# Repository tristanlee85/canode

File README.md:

# canode: dual-CAN vehicle interface

A small STM32G0B1 board with **two CAN channels**, USB-C and a 12 V automotive input, for sniffing, gatewaying and inline (man-in-the-middle) modification of vehicle CAN traffic. CAN1 faces the car, CAN2 faces the module. A typical job: suppress auto start-stop or change a body-module behaviour without touching the factory wiring.

Target vehicles: 2021 Ford Bronco Sport (HS/MS-CAN), 2019 Chevrolet Silverado 3500 (GM Global A), possibly a 2016 BMW F80. All three use classic CAN, not CAN-FD.

> **Status: rev A, ready to order.** The design passes ERC and DRC, the footprints and parts have been checked against datasheets and LCSC stock, and the power input has been simulated against the 35 V suppressed load dump and ISO 7637-2 pulse 2a. Before ordering, confirm J2's pin order and U1's pin-1 mark in JLC's placement preview (see [Known limits](#known-limits)). Firmware builds and its logic is unit-tested, but nothing has run on hardware yet.

| | |
|---|---|
| MCU | STM32G0B1CEU6 (UFQFPN-48): Cortex-M0+ 64 MHz, 2× FDCAN, crystal-less USB FS, 512 KB flash |
| CAN | 2× SN65HVD230 (3.3 V, classic CAN to 1 Mbit/s); held in standby by hardware until firmware enables them; optional 120 Ω termination per channel (solder jumper) |
| Power | 12 V input (PTC, 1500 W TVS, reverse-polarity diode, RC filter) or USB, into a TPS7B69 40 V LDO; sleeps at about 1 mA when the buses go quiet |
| I/O | Four 0–36 V sense inputs (VBAT, AUX_IN, IGN_IN, AUX_IN2), harness-ID input, AUX_OUT low-side switch, SWD, UART, 4 spare GPIO |
| Harness | Molex Micro-Fit 3.0, 2×6 on the board; universal pigtail to a per-vehicle T-harness |
| Board | 85 × 50 mm, 2 layers; every SMD part on top for JLCPCB Economic assembly |
| Enclosure | 90 × 55 × 20 mm MJF nylon, ordered from JLC3DP (no printer needed) |

## What it can do

Auto start-stop suppression is one rule set on a general-purpose tool. Every channel boots listen-only, and anything that transmits needs an explicit command (see [Safety model](#firmware)).

**With today's firmware** (built and unit-tested, not yet run on hardware):

| Capability | How |
|---|---|
| **Telemetry capture, both buses at once** | Streams every frame from the car side (CAN1) and the module side (CAN2), timestamped, in candump format over USB. A fully loaded 1 Mbit/s bus fits. `firmware/scripts/capture.py` saves a drive to a file that opens in SavvyCAN, can-utils or `tools/canlog`. |
| **Signal hunting** | Log while you press a button or change a setting, then diff the capture in `tools/canlog` to see which ID and byte moved. |
| **Silent sniffing** | Bus-monitoring mode sends no ACKs, and `rslisten high` also turns the transceiver's driver off in hardware. |
| **Inline filter / block / rewrite** | Per-direction rules between the car and one module: pass, drop, or rewrite the ID or any data nibble. Uses beyond start-stop include: forcing a setting the module would otherwise reset at key-on (drive mode, comfort settings); hiding a message a retrofit module objects to; remapping IDs so a module from another trim or year accepts the car's messages. |
| **Bench work on a module** | Put a module on the bench with canode as its "car": send frames by hand, watch its replies, and check error counters and bus-off state (`status`). |
| **Bus health** | Per-channel error counters, error-passive and bus-off flags, and lost-frame counts. Useful for chasing a flaky connector or a wrong bitrate. |

**Hardware is ready; the firmware still needs writing:**

| Capability | Uses |
|---|---|
| **Live decoded telemetry** | Decode known signals on the board (from a DBC) and stream values instead of raw frames: speed, RPM, gear, coolant and transmission temperature, boost, fuel level. That could feed a phone app or a custom gauge, e.g. trans temp while towing with the Silverado. |
| **OBD-II / UDS queries** | Ask ECUs for PIDs or read trouble codes, for data that isn't broadcast. It transmits, and it needs the tap point to be on the bus the ECU listens to. |
| **CAN-triggered output (AUX_OUT)** | The low-side switch drives a relay coil or LED, or pulls down a factory switch input. Examples: auxiliary lights with the high beams, a light bar, a reverse-camera or reverse-light trigger, a fan on high trans temp. |
| **Physical input (AUX_IN, 0–36 V)** | An added switch or an ignition/accessory feed selects a rule set or sends a message, e.g. a dash button that toggles a mode. |
| **Battery monitoring (VBAT sense)** | Log battery voltage, cranking dips and parked drain; cut AUX_OUT loads at low voltage. |
| **Permanent install** | Rules live in RAM today, and the gateway is off after every power-up. A fit-and-forget start-stop install needs rules saved to flash, plus an explicit opt-in to start the gateway at boot. |
| **Add-ons on J5** | The spare I2C/UART pins could take a Bluetooth or Wi-Fi module for a wireless console, an SD card or SPI flash for standalone logging, or a small display. |

**Out of scope:** CAN-FD frames (the transceivers are classic CAN, up to 1 Mbit/s), LIN, FlexRay and automotive Ethernet.

## What it looks like

| Closed, harness and USB connected | Exploded |
|---|---|
|  |  |
| **Lid off** | **Top view, cm scale** |
|  |  |

The harness plugs into J2 through the lid. USB-C, the three status LEDs and the RESET/BOOT poke-holes are reachable with the lid on. The debug headers and termination jumpers are inside, two screws away. Mount it with the screw/zip-tie ears or VHB tape. Design, ordering and assembly: [`hardware/enclosure/`](hardware/enclosure/README.md).

<details><summary>Board top and bottom</summary>

</details>

Regenerate every image with `make renders` (KiCad 10, Blender, uv; about 10 minutes).

## In the car: one board, a harness per vehicle

canode lives at each vehicle's **CAN gateway**, as a man-in-the-middle on one bus: CAN1 faces the car, CAN2 faces the gateway. The board, the enclosure and a short pigtail (J2 to a universal 12-way Deutsch DTM connector) are the same for every vehicle. Only the T-harness changes: it plugs in between the gateway and its factory connector and branches off to the DTM. Nothing in the car is cut or spliced, nothing is written to any module, and unplugging the harness puts the car back to stock. Details: [`hardware/README.md`](hardware/README.md#harness-pigtail-and-t-harness).

| Ford Bronco Sport (GWM) | Chevrolet Silverado 3500 |
|---|---|
|  |  |
| **BMW F80 M3** | |
|  | |

The housings in these renders are **representative**. Pin count, colour and lock style suggest each connector family, but they are not dimensioned copies of the OEM parts. Each real harness is built once the gateway connector and the bus to intercept have been confirmed on the car.

| T-harness wire | Goes to |
|---|---|
| Every pin except the intercepted CAN pair | straight through, factory connector ↔ gateway |
| CAN H/L from the factory connector (car side) | J2 pin 2 CAN1_H, pin 8 CAN1_L |
| CAN H/L into the gateway | J2 pin 3 CAN2_H, pin 9 CAN2_L |
| The gateway's battery feed (or a fused tap) | J2 pin 1 +12 V |
| The gateway's ground | J2 pin 7 GND |
| Ignition or accessory feed, if the connector has one | J2 pin 5 IGN_IN |
| ID resistor (one value per vehicle) | between J2 pin 11 HARNESS_ID and pin 12 GND |

Notes:
- **Ford Bronco Sport:** plug-in start-stop eliminators for this vehicle sit inline between the factory harness and the gateway module behind the OBD port under the steering column ([example install](https://www.4dtech.com/ford-bronco-sport-21-22-start-stop-eliminator)). That is a natural canode tap point too.
- **Silverado and F80:** canode goes at the CAN gateway here too, not at the start-stop switch where the common eliminators plug in. On GM Global A trucks the BCM usually does the gateway job, and on the F30/F80 family the central gateway is built into the FEM. Confirm both from service info.
  - The Silverado's low-speed GMLAN is single-wire CAN, which canode's transceivers can't drive. Pick a two-wire bus to intercept.
  - The F80's FlexRay and Ethernet are out of scope; its K-CAN and PT-CAN buses are fine.
- **One bus at a time:** a central gateway has several bus pairs on its connector. canode intercepts one of them, so each T-harness picks the bus that carries the messages you want to change.
- **Termination:** cutting a bus into two segments can leave one of them unterminated, for example when the module was an end node. Measure each segment (about 60 Ω is correct) and bridge JP1/JP2 only where a segment needs it.

## Harness connector (J2, Molex Micro-Fit 3.0 2×6)

| Pin | Signal | Pin | Signal |
|---|---|---|---|
| 1 | +12 V (battery or switched) | 7 | GND |
| 2 | CAN1_H (car side) | 8 | CAN1_L |
| 3 | CAN2_H (module side) | 9 | CAN2_L |
| 4 | AUX_IN (0–36 V sense) | 10 | AUX_OUT (low-side switch) |
| 5 | IGN_IN (0–36 V sense: ignition / accessory feed) | 11 | HARNESS_ID (resistor to GND in the T-harness) |
| 6 | AUX_IN2 (0–36 V sense) | 12 | GND (ID resistor return, shield drain) |

Each H/L pair sits on adjacent pins across the two rows, so twisted pairs land cleanly. The pinout is also on the board's back silkscreen and engraved on the enclosure.

**HARNESS_ID** lets the firmware tell which T-harness is plugged in. The board pulls the pin up to 3.3 V through 10 kΩ, and each T-harness puts its own resistor from pin 11 to pin 12. The ADC (PB12) then reads 3.3 V × R / (R + 10 k), so the firmware could pick that vehicle's profile automatically. That auto-selection isn't written yet; the read-only firmware doesn't use it. Suggested values, all E12 and well apart on the ADC: open = bench or no harness, 0 Ω = reserved, 1 k, 2.2 k, 4.7 k, 10 k, 22 k, 47 k.

All three 0–36 V inputs (AUX_IN, IGN_IN, AUX_IN2) use the same 100k:10k divider and 100 nF filter as VBAT sense, so any vehicle voltage, including a 24 V jump start or a 35 V load dump, is safe on them. They read 12 V-active signals directly. A ground-switched signal needs a pull-up to 12 V in the T-harness.

## Quick start (macOS)

```bash
scripts/setup_mac.sh            # KiCad 10, ngspice, ARM GCC, CMake, OpenOCD, dfu-util, Blender, Python venv
source .venv/bin/activate
make check                      # pinout check + ERC + DRC + firmware and tool unit tests
make fab                        # JLC upload files -> build/fab/
make firmware                   # canode + NUCLEO-G0B1RE images -> firmware/build/
make sim                        # ngspice power-input simulations
make renders                    # board + enclosure renders
```

Ordering steps are in [`hardware/README.md`](hardware/README.md#ordering-at-jlcpcb).

## Validation

The full plan, with pass criteria, is in [`validation/README.md`](validation/README.md); dated results are in [`validation/reports/`](validation/reports/).

| Check | Result |
|---|---|
| Netlist vs design table | ✅ 61 parts, 45 nets, 0 mismatches |
| MCU pinout vs ST's pin data (UFQFPN-48) | ✅ 32/32 incl. exposed pad on GND |
| Schematic ERC | ✅ 0 errors |
| DRC + schematic parity | ✅ 0 errors, parity clean |
| Pad-by-pad net parity (board vs netlist) | ✅ 242/242 pads |
| Footprint ↔ datasheet pinout | ✅ all match; J2's physical pin order still to confirm against the Molex drawing |
| Reference-design comparison | ✅ crystal load caps corrected (30 → 20 pF) |
| LCSC stock | ✅ out-of-stock MCU, TVS and LED replaced |
| Analog simulation | ✅ 35 V suppressed load dump, ISO 7637-2 pulse 2a, reverse battery, crank (after the [protection update](validation/reports/2026-11-09_protection.md)) |

## Firmware

Bare-metal C, CMake and `arm-none-eabi-gcc`, with ST's HAL for clocks/GPIO/FDCAN and TinyUSB for the USB virtual serial port. It builds for canode and for a **NUCLEO-G0B1RE** dev board, so you can start testing before the PCB arrives. Shell commands, flashing and the safety model are in [`firmware/README.md`](firmware/README.md).

**Safety model.** Both channels boot in FDCAN bus-monitoring mode (no ACKs, no transmit), with the transceivers held in standby until each controller is configured. Transmitting (normal mode, the gateway, sending a frame) requires an explicit shell command for one named channel, and nothing re-enables it automatically: not a bus-off recovery, a reboot, or a self-test.

## Known limits

1. **Load dump.** The input is built for the 35 V *suppressed* load dump that modern alternators produce: the SMCJ33A TVS doesn't conduct, and a 10 Ω + 10 µF filter keeps fast spikes under 30 V at the LDO. The board is **not** rated for an *unsuppressed* load dump (87 V). Details: [`validation/reports/2026-11-09_protection.md`](validation/reports/2026-11-09_protection.md).
2. **Quiescent current on an always-hot feed** is about 9 mA while the MCU is awake. The firmware now sleeps (STM32 Stop 1) after 60 s of bus silence and wakes on CAN1, CAN2 or a UART key. The estimated sleep draw is ~0.9 mA, plus ~0.1–0.17 mA for the always-on power LED (R1 is now 4.7 kΩ), so about 1 mA in total. A running gateway sleeps too and resumes on wake; while asleep, the car and module sides are disconnected, and the frame(s) that wake it aren't forwarded. Sleep is untested on hardware. Details: [`firmware/README.md`](firmware/README.md#sleep-stop-1).
3. **Unverified before ordering:** J2's physical pin order against the Molex 43045 drawing, and U1's pin-1 mark in JLC's placement preview (the package changed to QFN).

## Repo map

| Path | What |
|---|---|
| `hardware/kicad/` | KiCad 10 project: **source of truth** |
| `hardware/fab/` | JLC upload files for rev A (regenerate with `make fab`) |
| `hardware/docs/` | Schematic PDF and renders |
| `hardware/enclosure/` | Parametric enclosure (build123d), STEP files, render pipeline |
| `hardware/3dmodels/` | Stand-in 3D models for parts KiCad's library lacks |
| `hardware/generator/` | One-shot scripts that created rev A (don't re-run) |
| `firmware/` | STM32G0B1 firmware + host unit tests |
| `validation/` | Pin check, ngspice simulations, validation plan and reports |
| `tools/canlog/` | Terminal CAN logger and byte-diff tool for STN adapters (OBDLink MX+) |
| `CLAUDE.md` | Context and rules for Claude Code sessions |

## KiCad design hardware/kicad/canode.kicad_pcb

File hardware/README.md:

# CAN node hardware, rev A (prototype)

This is a 2-channel CAN interface board for in-vehicle sniffing and gatewaying. It is built around an STM32G0B1, which has two FDCAN controllers and crystal-less USB. It has two 3.3 V CAN transceivers and a 12 V automotive input, and it fits JLCPCB's **Economic PCBA**: every SMD part is on the top side, and only the through-hole connectors are left for you to solder by hand.

> **Status: unreviewed first pass.** The schematic was generated from a parts and nets list, and the board was **autorouted** (Freerouting). DRC shows 0 unrouted nets and 0 clearance errors. Please go through the checklist at the bottom before ordering.

## What's in the folder

| Path | What it is |
|---|---|
| `kicad/canode.kicad_pro` | **Open this in KiCad 10.** Generated with KiCad 7.0, upgraded to KiCad 10 format on 2026-11-09. |
| `kicad/canode.kicad_sch` | Single-sheet schematic. Nets connect by **name labels**, not drawn wires: two pins with the same label are connected. |
| `kicad/canode.kicad_pcb` | 2-layer, 85 × 50 mm board with GND pours on both layers and stitching vias. |
| `kicad/canode.kicad_sym`, `sym-lib-table` | Project library holding the one custom symbol (TPS7B6933). |
| `fab/canode_gerbers_JLC.zip` | **Upload this to JLCPCB.** Gerbers and Excellon drills. |
| `fab/canode_BOM_JLC.csv` | BOM for JLC assembly (Comment / Designator / Footprint / LCSC Part #). |
| `fab/canode_CPL_JLC.csv` | Pick-and-place file (Designator / Mid X / Mid Y / Layer / Rotation). |
| `fab/canode_HAND_SOLDER.csv` | Parts JLC does **not** place: J2 Micro-Fit and the J3/J4/J5 pin headers. |
| `docs/canode_schematic.pdf` | Schematic PDF for reviewing on paper (regenerate: `kicad-cli sch export pdf`). |
| `docs/renders/` | 3D board and enclosure renders (`make renders`). |
| `3dmodels/` | Stand-in 3D models for J1, J2, SW1/SW2 and the mating plug (KiCad has none). |
| `enclosure/` | Parametric MJF-nylon enclosure, STEP files and the render pipeline. |
| `scripts/jlc_fab.py` | Regenerates the JLC files from the KiCad project after you edit it (`make fab`). |
| `generator/` | Python scripts that produced the first version. `design.py` defines the parts, nets and LCSC numbers; `layout.py` defines placement. Written against the KiCad 7 Python API; once you edit in KiCad, treat KiCad as the source of truth and don't re-run it (it re-autoroutes and overwrites the board). |

## Block summary

**Power.** The J2 12 V pin feeds a 500 mA PTC (F1), then a 1500 W unidirectional TVS (D3, SMCJ33A, 36.7 V minimum breakdown), then an SS36 diode (D1). An RC filter (R17 10 Ω, C1 10 µF/50 V) follows the diode, then a 40 V-rated 3.3 V LDO (U2, TPS7B6933-Q1, 15 µA quiescent). The TVS stays off in a 35 V suppressed load dump. The filter holds fast spikes (ISO 7637-2 pulse 2a) under 30 V at the LDO. USB VBUS is diode-ORed onto the LDO input through D2, after the filter, so the board runs from USB on the bench or from the car in the vehicle. If the battery is connected backwards, D1 blocks and the TVS conducts until the PTC trips. Not rated for an unsuppressed (87 V) load dump. See `validation/reports/2026-11-09_protection.md`.

**MCU.** STM32G0B1CEU6 (UFQFPN-48, 512 KB flash; changed from the LQFP-48 CBT6 on 2026-11-09 because the LQFP was out of stock everywhere. Same pin numbering. The exposed pad is soldered to GND through a 3×3 via grid) with a 12 MHz crystal for an accurate CAN bit clock. USB runs from the internal 48 MHz oscillator with clock recovery (CRS).

**CAN (×2).**
- Each channel has an SN65HVD230 transceiver and an NUP2105L CAN ESD diode.
- Each has a 120 Ω terminator that only connects when you bridge a solder jumper (JP1 / JP2). The jumpers are **open by default**, so termination is off.
- The Rs pin has a **10k pull-up**, so the transceiver sits in **standby (not driving the bus)** until firmware pulls Rs low. The bus stays silent while the MCU is resetting, blank or crashed.
- For true listen-only, use FDCAN *bus monitoring* mode, which sends no ACKs, with Rs low.

**Sense and output.**
- VBAT, AUX_IN, IGN_IN and AUX_IN2 each go to an ADC pin through a 100k:10k divider with a 100 nF filter. Full scale is about 36 V, about 9 mV per count.
- HARNESS_ID (J2 pin 11): 10 kΩ pull-up to 3.3 V, then 10 kΩ + 100 nF into the ADC. The T-harness puts an ID resistor from pin 11 to pin 12 (GND). A wiring fault that puts 12–36 V on the pin pushes at most ~3 mA into the pin's clamp and the 3.3 V rail through 10 kΩ.
- AUX_OUT is a low-side AO3422 (55 V) switch with an SS36 (60 V) flyback diode to VBAT, through R18 (2.2 Ω), which keeps reverse-battery current out of Q1's body diode. It can drive a relay coil or an LED, or pull down a factory switch input.

**Debug.** SWD header (J3), UART header (J4), 4 spare GPIO (J5), RESET and BOOT buttons, and power / two status LEDs.

### J2: Molex Micro-Fit 3.0, 2×6 vertical (43045-1212)

| Pin | Signal | Pin | Signal |
|---|---|---|---|
| 1 | +12 V (battery or switched) | 7 | GND |
| 2 | CAN1_H (car side) | 8 | CAN1_L |
| 3 | CAN2_H (module side) | 9 | CAN2_L |
| 4 | AUX_IN (0–36 V sense) | 10 | AUX_OUT (low-side switch) |
| 5 | IGN_IN (0–36 V sense: ignition / accessory feed) | 11 | HARNESS_ID (resistor to GND in the T-harness) |
| 6 | AUX_IN2 (0–36 V sense) | 12 | GND (ID resistor return, shield drain) |

H/L pairs are stacked across the two rows, so each twisted pair lands on adjacent pins. The pinout is also printed on the back silkscreen.

### MCU pin map (for firmware)

| Function | Pin | Notes |
|---|---|---|
| FDCAN1 RX / TX | PD0 / PD1 | AF3 |
| CAN1 Rs (standby) | PD2 | drive LOW to enable transceiver |
| FDCAN2 RX / TX | PB0 / PB1 | AF3 |
| CAN2 Rs (standby) | PB2 | drive LOW to enable transceiver |
| USB DM / DP | PA11 / PA12 | |
| HSE | PF0 / PF1 | 12 MHz, 20 pF load caps |
| VBAT sense | PA0 (ADC IN0) | V = adc × 3.3/4096 × 11 |
| AUX_IN sense | PA1 (ADC IN1) | same divider |
| IGN_IN sense | PB10 (ADC IN11) | same divider |
| AUX_IN2 sense | PB11 (ADC IN15) | same divider |
| HARNESS_ID | PB12 (ADC IN16) | 10k pull-up; V = 3.3 × R / (R + 10k) |
| AUX_OUT gate | PA8 | TIM1_CH1 if you want PWM |
| LED1 / LED2 | PA5 / PA6 | active high |
| Debug UART | PA2 TX / PA3 RX | USART2 |
| Spare GPIO | PB6, PB7, PB8, PB9 | PB6/PB7 = I2C1 or USART1 |
| SWD | PA13 SWDIO / PA14 SWCLK | PA14 is also BOOT0 |

## Harness: pigtail and T-harness

canode never plugs straight into a car. Three pieces sit between them, so one board serves every vehicle:

```
canode J2 ──pigtail (~20 cm)──▶ universal inline connector ◀── per-vehicle T-harness ──▶ factory connector ⇄ CAN gateway
 (Micro-Fit 2×6)                 (12-way, sealed)               (made once per vehicle)
```

1. **Pigtail (the same for every car).** It runs from a Micro-Fit 43025-1200 housing on J2 to the universal connector, wired pin for pin (J2 pin n = universal pin n). Use 20–22 AWG automotive wire (TXL/GXL), and twist each CAN pair (2/8 and 3/9) at about 30–40 twists per metre.
2. **Universal inline connector.** The suggested part is a **Deutsch DTM 12-way** pair: sealed, cheap, and stocked everywhere. The pigtail end is a DTM04-12PA receptacle with pin contacts and a WM-12P wedge. The T-harness end is a DTM06-12SA plug with socket contacts and a WM-12S wedge. Contacts are size 20, crimped with the matching tool. Confirm the part numbers against the TE/Deutsch catalogue before ordering. This uses the usual automotive convention: the side that carries battery power (the T-harness) gets the **sockets**, so no live pin is exposed when it's unplugged. canode's side has no power on its pins when unplugged.
3. **T-harness (one per vehicle).** It has an inline male/female pair matching the factory connector at that vehicle's CAN gateway, plus the DTM06 branch:
   - every factory pin passes straight through, except the one CAN pair being intercepted;
   - the car side of that pair goes to pins 2/8 (CAN1) and the gateway side to pins 3/9 (CAN2);
   - +12 V comes from the gateway's battery feed, through an inline 2 A fuse close to the tap, to pin 1, and its ground goes to pin 7;
   - an ignition or accessory feed, if the connector has one, goes to pin 5;
   - the harness's ID resistor sits between pins 11 and 12, inside the DTM06 boot.

Which bus, which pins and which connector to use are per-vehicle research (service-info pinouts plus a sniff on the car). Record each finished harness in `hardware/harness/<vehicle>.md` with its connector part numbers, pin table and ID resistor value.

## Ordering at JLCPCB

1. **Upload `canode_gerbers_JLC.zip`.** JLC should detect a 2-layer, 85 × 50 mm board.
2. **Choose the board options.**
   - 1.6 mm thickness, any color, HASL lead-free or ENIG.
   - Leave *Remove order number* at its default (or pay to remove it).
   - The PCB minimum is 5 boards.
3. **Turn on PCB Assembly.**
   - Choose **Economic**, **Top side**, and **2** for the assembly quantity.
4. **Upload the BOM and CPL.**
   - BOM is `canode_BOM_JLC.csv`; CPL is `canode_CPL_JLC.csv`.
   - Every line should match an LCSC part. If one shows out of stock, pick an equivalent and note the change.
5. **Check part rotation and polarity in the placement preview.** KiCad and JLC sometimes disagree on a footprint's zero angle. Check that pin 1 or the polarity mark lines up on:
   - U1 (QFN pin-1 corner mark; the part changed from LQFP, so check this one carefully)
   - U2 (SOT-223 tab)
   - U3 and U5 (SOIC pin 1)
   - U4, U6 and Q1 (SOT-23)
   - U7 (SOT-23-6)
   - D1, D2, D3 and D7 (cathode band)
   - D4, D5 and D6 (LED cathode)
   - J1 (USB-C)

   You can rotate parts right in the preview, and JLC's DFM engineers also check.
6. **Order the hand-solder parts separately** (Digi-Key / Mouser / LCSC):
   - Molex **43045-1212**, plus mating housing 43025-1200 and crimp terminals 43030-0001 for the pigtail (see [Harness](#harness-pigtail-and-t-harness)).
   - Straight 2.54 mm headers: 1×5, 1×3 and 1×6.

Ballpark cost: about $2 for the PCBs, plus Economic PCBA setup (about $8 + stencil). Expect 8 extended-part fees at $3 each (per `validation/reports/2026-11-09_lcsc.md`) on top of parts. That comes to something like $40–60 for 2 assembled boards before shipping; JLC's quote is the real number.

## First power-up and programming

1. Power from USB-C only. The PWR LED should light and 3.3 V should appear on J3 pin 1.
2. A blank STM32G0 boots straight into the ROM **USB DFU bootloader**, so it shows up as "STM32 BOOTLOADER". Flash it with `dfu-util` or STM32CubeProgrammer, with no debugger needed. After the first flash, use SWD (J3, ST-Link) or re-enter DFU from firmware.
3. The BOOT button only works after you set the option bytes **nBOOT_SEL = 0** (use the BOOT0 pin). With the factory defaults it is ignored.
4. Bench test: bridge JP1 and JP2 to terminate both buses and connect CAN1↔CAN2 with a short twisted pair. Each channel can then talk to the other in loopback.

## Review checklist (things I want your eyes on)

**Electrical decisions**
- [x] **Input TVS (D3) and protection chain.** Done 2026-11-09: SMCJ33A (1500 W, 36.7 V min breakdown) replaces the SMBJ24A, which would have absorbed 16–49 J in a 35 V suppressed load dump. Added R17 10 Ω + C1 10 µF ahead of the LDO and R18 2.2 Ω in the D7 path. Simulated: D3 carries 0 A at 35 V, the LDO sees ≤ 34.5 V, Q1 ≤ 49.4 V of 55 V (`validation/reports/2026-11-09_protection.md`). Still not rated for an *unsuppressed* load dump.
- [x] **PTC voltage rating.** With D3 sized as above, F1 only sees ≤ 13 V (when tripped by a reversed battery), so the 30 V BSMD1206 stays. No 60 V PTC exists in 1206 at JLC. Its 40 A Imax is the tightest margin left: 37.8 A peak in the reverse-battery sim.
- [x] **AUX_OUT FET.** Now AO3422 (55 V). Flyback diode D7 and the OR diodes D1/D2 are now SS36 (60 V); D2 saw ~44 V reverse in ISO 7637-2 pulse 2a.
- [x] **Quiescent draw on an always-hot 12 V feed.** Awake: ~9 mA (the MCU at 64 MHz dominates). The firmware now drops to STM32 Stop 1 after 60 s of bus silence and wakes on CAN1, CAN2 or a UART key. R1 went from 1 kΩ to 4.7 kΩ so the always-on PWR LED draws ~0.1–0.17 mA. Estimated sleep total: about 1 mA (two SN65HVD230s in standby 0.74 mA, VBAT divider 0.11 mA, LED, LDO, MCU). Measure on the bench (`firmware/README.md`, Sleep).
- [x] **Crystal load caps.** Changed 30 → 20 pF (step 7: ST's ~10 pF stray estimate left almost no oscillator start-up margin at 30 pF). Fine-tune if the measured frequency is off.
- [ ] **CAN transceivers.** SN65HVD230 (3.3 V) is standard and interoperates with 5 V CAN, but it is specified only to 1 Mbps. That covers classic CAN; none of the target vehicles use CAN-FD. If FD is ever needed, TCAN337GDR is a true drop-in (TCAN1044 needs a 5 V supply this board doesn't have). See `validation/reports/2026-11-09_lcsc.md`.

**Layout**
- [ ] **Autorouted, not hand-optimized.** Signal tracks are 0.25 mm; power tracks are 0.5 mm (VBAT / VIN / VBUS / AUX_OUT) and 0.3 mm (3V3 / GND). USB D+/D- are not length-matched; at 12 Mbps full-speed that is fine. Re-routing the crystal and USB pairs by hand is the main tidy-up if you want it.
- [ ] **USB-C overhang.** Check in the 3D viewer (`Alt+3`) that J1 sits flush with the board edge.
- [x] **Thermal relief on U5 pin 2** (GND): fixed 2026-11-09 by giving that pad a solid zone connection.
- [x] **Overlapping silk labels** (C5 / Y1): fixed 2026-11-09 by moving Y1's label 2.2 mm left.

**Process**
- [x] **Re-run ERC and DRC.** Done with KiCad 10 on 2026-11-09: 0 ERC errors, 0 DRC errors, schematic parity clean. See `validation/reports/2026-11-09_erc.md` and `2026-11-09_drc.md`.
- [ ] **Check LCSC stock** at order time; the numbers were checked against JLC's catalog in Nov 2026.

## Modern KiCad crash course (since ExpressPCB)

- **Projects.** Schematic, PCB and rules are tied together by `.kicad_pro`. Edit the schematic, then press **F8** (*Update PCB from Schematic*) in the PCB editor. Footprints stay linked to their symbols by ID, so moved parts keep their positions.
- **Net labels.** This schematic uses "label stubs" instead of drawn wires. Hover a label and press the backtick key (`` ` ``) to highlight that net everywhere. To tidy it up, delete the stubs and draw wires; connectivity is identical.
- **Routing tools.**
  - **X** routes a track; **V** while routing drops a via.
  - **D** drags a track and its neighbors follow.
  - **B** refills the copper zones after you edit tracks.
  - **Edit → Global Deletions… (Tracks)** if you want to start the routing over.
- **Board Setup** (File → Board Setup) holds the net classes and design rules. Power/Supply classes already set the wider tracks.
- **Fab outputs**: run `make fab` from the repo root (writes `build/fab/`), or use File → Fabrication Outputs. The "Fabrication Toolkit" plugin (Plugin & Content Manager) is a GUI alternative.

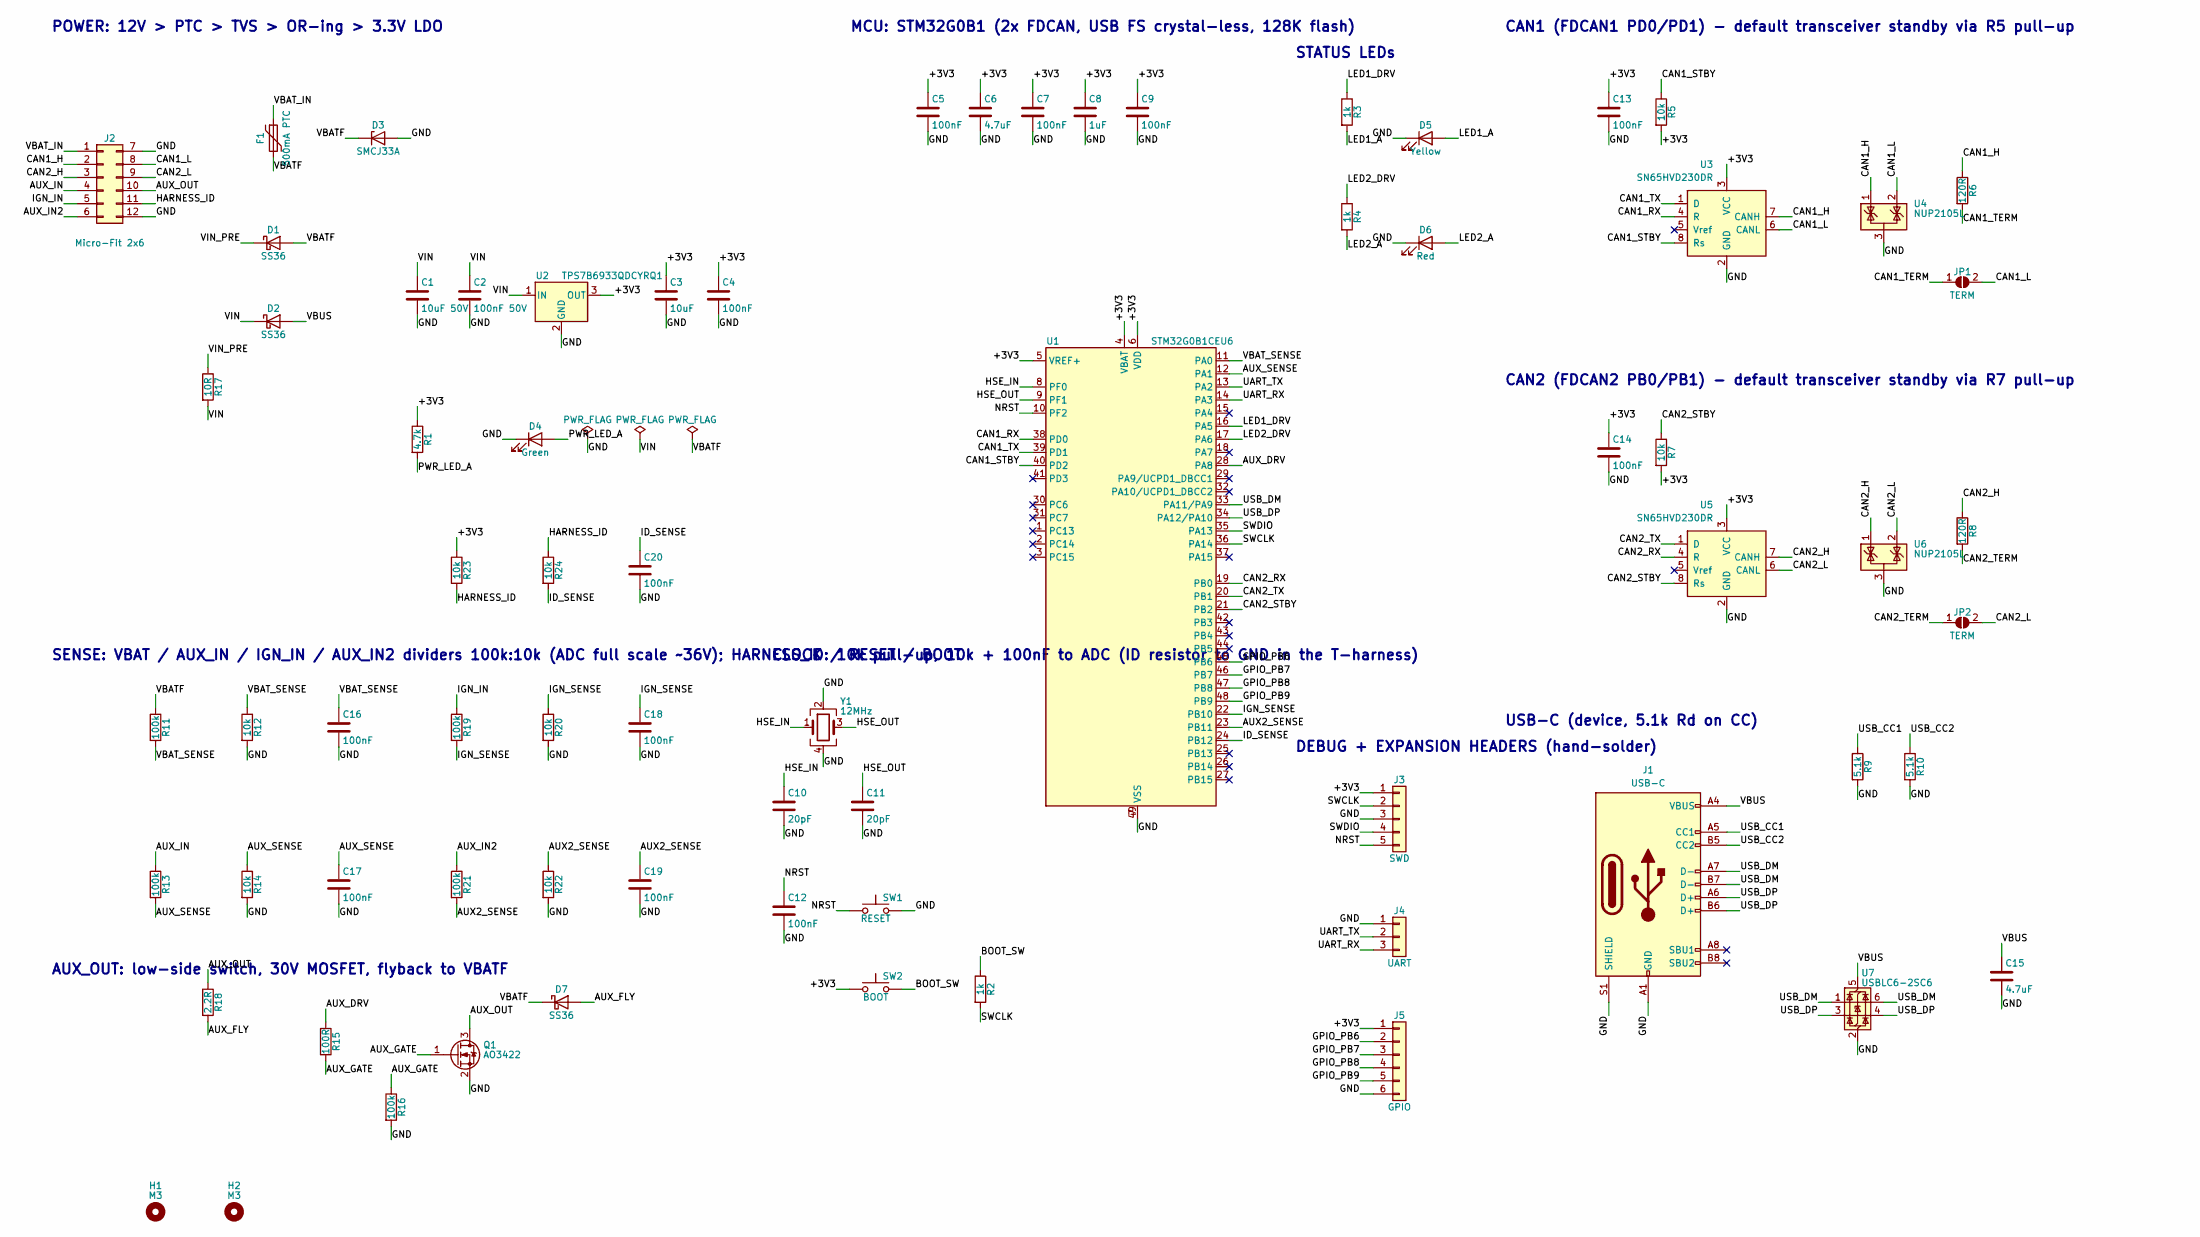
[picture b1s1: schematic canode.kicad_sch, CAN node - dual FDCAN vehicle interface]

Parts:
C1: 10uF 50V; C_1206_3216Metric; MPN CL31A106KBHNNNE; LCSC C13585
C2: 100nF 50V; C_0603_1608Metric; MPN CL10B104KB8NNNC; LCSC C14663
C3: 10uF; C_0603_1608Metric; MPN CL10A106MQ8NNNC; LCSC C96446
C4, C5, C7, C9, C12, C13, C14, C16, C17, C18, C19, C20: 100nF; C_0603_1608Metric; MPN CL10B104KB8NNNC; LCSC C14663
C6, C15: 4.7uF; C_0805_2012Metric; MPN CL21A475KAQNNNE; LCSC C1779
C8: 1uF; C_0603_1608Metric; MPN CL10A105KB8NNNC; LCSC C15849
C10, C11: 20pF; C_0603_1608Metric; MPN CL10C200JB8NNNC; LCSC C1648
D1, D2, D7: SS36; D_SMA; MPN SS36; LCSC C16015
D3: SMCJ33A; D_SMC; MPN SMCJ33A-13-F (Diodes Inc); LCSC C135162
D4: Green; LED_0805_2012Metric; MPN Green 0805 LED; LCSC C2297
D5: Yellow; LED_0603_1608Metric; MPN KT-0603Y; LCSC C2287
D6: Red; LED_0603_1608Metric; MPN Red 0603 LED; LCSC C2286
F1: 500mA PTC; Fuse_1206_3216Metric; MPN BSMD1206-050-30V; LCSC C883126
H1, H2: M3; MountingHole_3.2mm_M3; JLC hand-solder / not assembled
J1: USB-C; USB_C_Receptacle_HRO_TYPE-C-31-M-12; MPN HRO TYPE-C-31-M-12; LCSC C165948
J2: Micro-Fit 2x6; Molex_Micro-Fit_3.0_43045-1212_2x06_P3.00mm_Vertical; MPN Molex 43045-1212; JLC hand-solder / not assembled
J3: SWD; PinHeader_1x05_P2.54mm_Vertical; MPN 1x5 2.54mm header; JLC hand-solder / not assembled
J4: UART; PinHeader_1x03_P2.54mm_Vertical; MPN 1x3 2.54mm header; JLC hand-solder / not assembled
J5: GPIO; PinHeader_1x06_P2.54mm_Vertical; MPN 1x6 2.54mm header; JLC hand-solder / not assembled
JP1, JP2: TERM; SolderJumper-2_P1.3mm_Open_RoundedPad1.0x1.5mm; MPN solder jumper (bridge = 120R terminatio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; JLC hand-solder / not assembled
Q1: AO3422; SOT-23; MPN AO3422; LCSC C37130
R1: 4.7k; R_0603_1608Metric; MPN 0603 1% resistor; LCSC C23162
R2, R3, R4: 1k; R_0603_1608Metric; MPN 0603 1% resistor; LCSC C21190
R5, R7, R12, R14, R20, R22, R23, R24: 10k; R_0603_1608Metric; MPN 0603 1% resistor; LCSC C25804
R6, R8: 120R; R_0603_1608Metric; MPN 0603 1% resistor; LCSC C22787
R9, R10: 5.1k; R_0603_1608Metric; MPN 0603 1% resistor; LCSC C23186
R11, R13, R16, R19, R21: 100k; R_0603_1608Metric; MPN 0603 1% resistor; LCSC C25803
R15: 100R; R_0603_1608Metric; MPN 0603 1% resistor; LCSC C22775
R17: 10R; R_0805_2012Metric; MPN 0805W8F100JT5E; LCSC C17415
R18: 2.2R; R_0805_2012Metric; MPN 0805W8F220KT5E; LCSC C17521
SW1: RESET; SW_Push_1P1T_XKB_TS-1187A; MPN TS-1187A-B-A-B; LCSC C318884
SW2: BOOT; SW_Push_1P1T_XKB_TS-1187A; MPN TS-1187A-B-A-B; LCSC C318884
U1: STM32G0B1CEU6; QFN-48-1EP_7x7mm_P0.5mm_EP5.6x5.6mm; MPN STM32G0B1CEU6; LCSC C2829190
U2: TPS7B6933QDCYRQ1; SOT-223-3_TabPin2; MPN TPS7B6933QDCYRQ1; LCSC C108471
U3, U5: SN65HVD230DR; SOIC-8_3.9x4.9mm_P1.27mm; MPN SN65HVD230DR; LCSC C12084
U4, U6: NUP2105L; SOT-23; MPN NUP2105LT1G; LCSC C14486
U7: USBLC6-2SC6; SOT-23-6; MPN USBLC6-2SC6; LCSC C7519
Y1: 12MHz; Crystal_SMD_3225-4Pin_3.2x2.5mm; MPN X322512MSB4SI (20pF CL); LCSC C9002

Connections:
/+3V3: C3.1, C4.1, C5.1, C6.1, C7.1, C8.1, C9.1, C13.1, C14.1, J3.1, J5.1, R1.1, R5.2, R7.2, R23.1, SW2.1, U1.4 (VBAT), U1.5 (VREF+), U1.6 (VDD), U2.3 (OUT), U3.3 (VCC), U5.3 (VCC)
/AUX2_SENSE: C19.1, R21.2, R22.1, U1.23 (PB11)
/AUX_DRV: R15.1, U1.28 (PA8)
/AUX_FLY: D7.2 (A), R18.2
/AUX_GATE: Q1.1 (G), R15.2, R16.1
/AUX_IN: J2.4, R13.1
/AUX_IN2: J2.6, R21.1
/AUX_OUT: J2.10, Q1.3 (D), R18.1
/AUX_SENSE: C17.1, R13.2, R14.1, U1.12 (PA1)
/BOOT_SW: R2.1, SW2.2
/CAN1_H: J2.2, R6.1, U3.7 (CANH), U4.1 (K)
/CAN1_L: J2.8, JP1.2 (B), U3.6 (CANL), U4.2 (K)
/CAN1_RX: U1.38 (PD0), U3.4 (R)
/CAN1_STBY: R5.1, U1.40 (PD2), U3.8 (Rs)
/CAN1_TERM: JP1.1 (A), R6.2
/CAN1_TX: U1.39 (PD1), U3.1 (D)
/CAN2_H: J2.3, R8.1, U5.7 (CANH), U6.1 (K)
/CAN2_L: J2.9, JP2.2 (B), U5.6 (CANL), U6.2 (K)
/CAN2_RX: U1.19 (PB0), U5.4 (R)
/CAN2_STBY: R7.1, U1.21 (PB2), U5.8 (Rs)
/CAN2_TERM: JP2.1 (A), R8.2
/CAN2_TX: U1.20 (PB1), U5.1 (D)
/GND: C1.2, C2.2, C3.2, C4.2, C5.2, C6.2, C7.2, C8.2, C9.2, C10.2, C11.2, C12.2, C13.2, C14.2, C15.2, C16.2, C17.2, C18.2, C19.2, C20.2, D3.2 (A), D4.1 (K), D5.1 (K), D6.1 (K), J1.A1 (GND), J1.A12 (GND), J1.B1 (GND), J1.B12 (GND), J1.S1 (SHIELD), J2.7, J2.12, J3.3, J4.1, J5.6, Q1.2 (S), R9.2, R10.2, R12.2, R14.2, R16.2, R20.2, R22.2, SW1.2, U1.7 (VSS), U1.49 (VSS), U2.2 (GND), U3.2 (GND), U4.3 (A), U5.2 (GND), U6.3 (A), U7.2 (GND), Y1.2, Y1.4
/GPIO_PB6: J5.2, U1.45 (PB6)
/GPIO_PB7: J5.3, U1.46 (PB7)
/GPIO_PB8: J5.4, U1.47 (PB8)
/GPIO_PB9: J5.5, U1.48 (PB9)
/HARNESS_ID: J2.11, R23.2, R24.1
/HSE_IN: C10.1, U1.8 (PF0), Y1.1
/HSE_OUT: C11.1, U1.9 (PF1), Y1.3
/ID_SENSE: C20.1, R24.2, U1.24 (PB12)
/IGN_IN: J2.5, R19.1
/IGN_SENSE: C18.1, R19.2, R20.1, U1.22 (PB10)
/LED1_A: D5.2 (A), R3.2
/LED1_DRV: R3.1, U1.16 (PA5)
/LED2_A: D6.2 (A), R4.2
/LED2_DRV: R4.1, U1.17 (PA6)
/NRST: C12.1, J3.5, SW1.1, U1.10 (PF2)
/PWR_LED_A: D4.2 (A), R1.2
/SWCLK: J3.2, R2.2, U1.36 (PA14)
/SWDIO: J3.4, U1.35 (PA13)
/UART_RX: J4.3, U1.14 (PA3)
/UART_TX: J4.2, U1.13 (PA2)
/USB_CC1: J1.A5 (CC1), R9.1
/USB_CC2: J1.B5 (CC2), R10.1
/USB_DM: J1.A7 (D-), J1.B7 (D-), U1.33 (PA11/PA9), U7.1 (I/O1), U7.6 (I/O1)
/USB_DP: J1.A6 (D+), J1.B6 (D+), U1.34 (PA12/PA10), U7.3 (I/O2), U7.4 (I/O2)
/VBATF: D1.2 (A), D3.1 (K), D7.1 (K), F1.2, R11.1
/VBAT_IN: F1.1, J2.1
/VBAT_SENSE: C16.1, R11.2, R12.1, U1.11 (PA0)
/VBUS: C15.1, D2.2 (A), J1.A4 (VBUS), J1.A9 (VBUS), J1.B4 (VBUS), J1.B9 (VBUS), U7.5 (VBUS)
/VIN: C1.1, C2.1, D2.1 (K), R17.2, U2.1 (IN)
/VIN_PRE: D1.1 (K), R17.1

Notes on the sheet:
CAN1 (FDCAN1 PD0/PD1) - default transceiver standby via R5 pull-up
CAN2 (FDCAN2 PB0/PB1) - default transceiver standby via R7 pull-up
STATUS LEDs
AUX_OUT: low-side switch, 30V MOSFET, flyback to VBATF
DEBUG + EXPANSION HEADERS (hand-solder)
SENSE: VBAT / AUX_IN / IGN_IN / AUX_IN2 dividers 100k:10k (ADC full scale ~36V); HARNESS_ID: 10k pull-up, 10k + 100nF to ADC (ID resistor to GND in the T-harness)
POWER: 12V > PTC > TVS > OR-ing > 3.3V LDO
USB-C (device, 5.1k Rd on CC)
MCU: STM32G0B1 (2x FDCAN, USB FS crystal-less, 128K flash)
CLOCK / RESET / BOOT

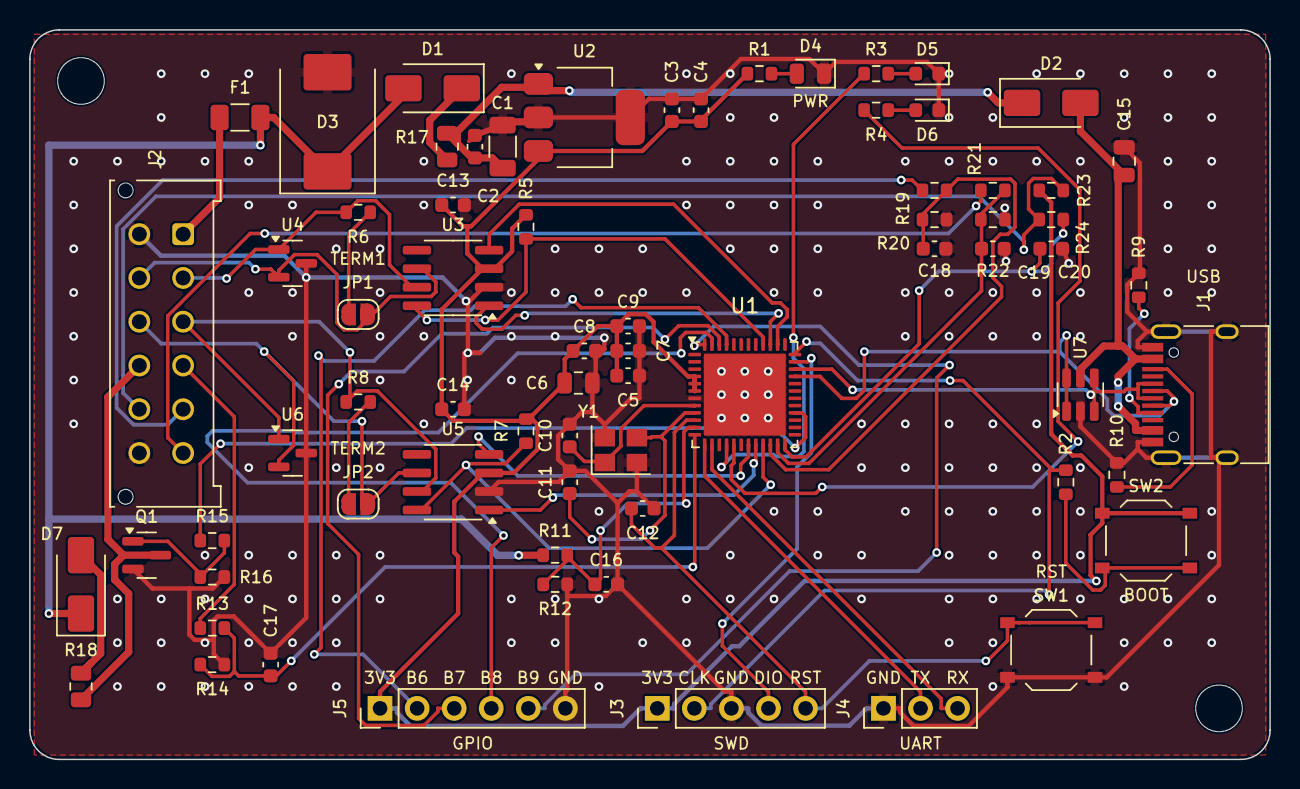
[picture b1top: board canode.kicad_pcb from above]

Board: 2 copper layers, 85.0 x 50.0 mm, 72 parts (0 on the bottom side), 53 nets.

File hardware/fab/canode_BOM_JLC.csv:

Comment,Designator,Footprint,LCSC Part #,Qty,MPN
10uF 50V,C1,C_1206_3216Metric,C13585,1,CL31A106KBHNNNE
100nF 50V,"C2,C4,C5,C7,C9,C12,C13,C14,C16,C17,C18,C19,C20",C_0603_1608Metric,C14663,13,CL10B104KB8NNNC
10uF,C3,C_0603_1608Metric,C96446,1,CL10A106MQ8NNNC
4.7uF,"C6,C15",C_0805_2012Metric,C1779,2,CL21A475KAQNNNE
1uF,C8,C_0603_1608Metric,C15849,1,CL10A105KB8NNNC
20pF,"C10,C11",C_0603_1608Metric,C1648,2,CL10C200JB8NNNC
SS36,"D1,D2,D7",D_SMA,C16015,3,SS36
SMCJ33A,D3,D_SMC,C135162,1,SMCJ33A-13-F (Diodes Inc)
Green,D4,LED_0805_2012Metric,C2297,1,Green 0805 LED
Yellow,D5,LED_0603_1608Metric,C2287,1,KT-0603Y
Red,D6,LED_0603_1608Metric,C2286,1,Red 0603 LED
500mA PTC,F1,Fuse_1206_3216Metric,C883126,1,BSMD1206-050-30V
USB-C,J1,USB_C_Receptacle_HRO_TYPE-C-31-M-12,C165948,1,HRO TYPE-C-31-M-12
AO3422,Q1,SOT-23,C37130,1,AO3422
4.7k,R1,R_0603_1608Metric,C23162,1,0603 1% resistor
1k,"R2,R3,R4",R_0603_1608Metric,C21190,3,0603 1% resistor
10k,"R5,R7,R12,R14,R20,R22,R23,R24",R_0603_1608Metric,C25804,8,0603 1% resistor
120R,"R6,R8",R_0603_1608Metric,C22787,2,0603 1% resistor
5.1k,"R9,R10",R_0603_1608Metric,C23186,2,0603 1% resistor
100k,"R11,R13,R16,R19,R21",R_0603_1608Metric,C25803,5,0603 1% resistor
100R,R15,R_0603_1608Metric,C22775,1,0603 1% resistor
10R,R17,R_0805_2012Metric,C17415,1,0805W8F100JT5E
2.2R,R18,R_0805_2012Metric,C17521,1,0805W8F220KT5E
RESET,"SW1,SW2",SW_Push_1P1T_XKB_TS-1187A,C318884,2,TS-1187A-B-A-B
STM32G0B1CEU6,U1,QFN-48-1EP_7x7mm_P0.5mm_EP5.6x5.6mm,C2829190,1,STM32G0B1CEU6
TPS7B6933QDCYRQ1,U2,SOT-223-3_TabPin2,C108471,1,TPS7B6933QDCYRQ1
SN65HVD230DR,"U3,U5",SOIC-8_3.9x4.9mm_P1.27mm,C12084,2,SN65HVD230DR
NUP2105L,"U4,U6",SOT-23,C14486,2,NUP2105LT1G
USBLC6-2SC6,U7,SOT-23-6,C7519,1,USBLC6-2SC6
12MHz,Y1,Crystal_SMD_3225-4Pin_3.2x2.5mm,C9002,1,X322512MSB4SI (20pF CL)

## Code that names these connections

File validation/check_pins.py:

#!/usr/bin/env python3
"""Validate the MCU pinout against ST's official pin data (STM32_open_pin_data).

Checks, for the STM32 (default ref U1):
  1. Every symbol pin number/name in the KiCad netlist matches ST's package pinout
     (catches a wrong or edited symbol).
  2. Every net in REQUIREMENTS lands on a pin that actually supports the required
     signal, and reports the GPIO alternate-function (AF) number to use in firmware.
  3. Power pins sit on the right rails.
  4. Flags pins whose net is not covered by REQUIREMENTS (so new nets get reviewed).

Usage:
  python3 validation/check_pins.py                     # exports netlist via kicad-cli
  python3 validation/check_pins.py --netlist foo.net   # use an existing netlist
Exit code 0 = all checks pass, 1 = failures.
"""
import argparse, subprocess, sys, tempfile, xml.etree.ElementTree as ET
from pathlib import Path

ROOT = Path(__file__).resolve().parents[1]
sys.path.insert(0, str(ROOT / "hardware" / "generator"))
from sexp import parse, find, find1  # noqa: E402

ST_REPO = "https://github.com/STMicroelectronics/STM32_open_pin_data.git"
CACHE = ROOT / "validation" / ".cache" / "STM32_open_pin_data"
MCU_XML = "STM32G0B1C(B-C-E)Ux.xml"   # UFQFPN48 (U1 = STM32G0B1CEU6); same GP pin numbering as LQFP48
EXPOSED_PAD = "49"                    # UFQFPN48 exposed pad: ST recommends soldering it to ground
GPIO_XML = "GPIO-STM32G0Bx_gpio_v1_0_Modes.xml"

# net name -> signal(s) the pin must support ("GPIO" = plain I/O is enough).
# A list means "any of these"; the first match is reported.
REQUIREMENTS = {
    "CAN1_RX": "FDCAN1_RX", "CAN1_TX": "FDCAN1_TX",
    "CAN2_RX": "FDCAN2_RX", "CAN2_TX": "FDCAN2_TX",
    "CAN1_STBY": "GPIO", "CAN2_STBY": "GPIO",
    "USB_DM": "USB_DM", "USB_DP": "USB_DP",
    "HSE_IN": "RCC_OSC_IN", "HSE_OUT": "RCC_OSC_OUT",
    "SWDIO": "SYS_SWDIO", "SWCLK": "SYS_SWCLK",
    "UART_TX": "USART2_TX", "UART_RX": "USART2_RX",
    "VBAT_SENSE": "ADC1_IN0", "AUX_SENSE": "ADC1_IN1",
    "IGN_SENSE": "ADC1_IN11", "AUX2_SENSE": "ADC1_IN15", "ID_SENSE": "ADC1_IN16",
    "AUX_DRV": ["TIM1_CH1", "GPIO"],
    "LED1_DRV": "GPIO", "LED2_DRV": "GPIO",
    "GPIO_PB6": ["I2C1_SCL", "USART1_TX", "GPIO"], "GPIO_PB7": ["I2C1_SDA", "USART1_RX", "GPIO"],
    "GPIO_PB8": "GPIO", "GPIO_PB9": "GPIO",
}
POWER = {"VDD": "+3V3", "VBAT": "+3V3", "VREF+": "+3V3", "VSS": "GND"}
SPECIAL = {"NRST": "NRST"}  # net -> substring that must appear in ST's pin name


def ensure_st_data():
    if not (CACHE / "mcu" / MCU_XML).exists():
        CACHE.parent.mkdir(parents=True, exist_ok=True)
        print(f"fetching ST pin data -> {CACHE}")
        subprocess.run(["git", "clone", "--depth", "1", "-q", ST_REPO, str(CACHE)], check=True)
    return CACHE / "mcu" / MCU_XML, CACHE / "mcu" / "IP" / GPIO_XML


def load_st(mcu_xml, gpio_xml):
    ns = {"m": "http://dummy.com"}
    def strip(t): return t.split("}", 1)[-1]
    pins = {}  # position -> list of (name, type, set(signals))
    for p in ET.parse(mcu_xml).getroot():
        if strip(p.tag) != "Pin": continue
        sigs = {s.get("Name") for s in p if strip(s.tag) == "Signal"}
        pins.setdefault(p.get("Position"), []).append((p.get("Name"), p.get("Type"), sigs))
    af = {}  # (pin base name, signal) -> AF string
    for gp in ET.parse(gpio_xml).getroot():
        if strip(gp.tag) != "GPIO_Pin": continue
        base = gp.get("Name").split("-")[0].split(" ")[0]
        for ps in gp:
            if strip(ps.tag) != "PinSignal": continue
            for v in ps.iter():
                if strip(v.tag) == "PossibleValue" and v.text and v.text.startswith("GPIO_AF"):
                    af[(base, ps.get("Name"))] = v.text
    return pins, af


def base_name(st_name):
    return st_name.split("-")[0].split(" ")[0]


def load_netlist(path, ref):
    net = parse(open(path).read())[0]
    out = {}
    for n in find(find1(net, "nets"), "net"):
        name = find1(n, "name")[1].lstrip("/")
        for node in find(n, "node"):
            if find1(node, "ref")[1] != ref: continue
            pf = find1(node, "pinfunction")
            pin = find1(node, "pin")[1]
            # KiCad 10 netlists append "_<pin number>" to pinfunction (e.g. "PA0_11"); strip it
            out[pin] = (name, pf[1].removesuffix(f"_{pin}") if pf else "")
    return out


def main():
    ap = argparse.ArgumentParser()
    ap.add_argument("--netlist")
    ap.add_argument("--sch", default=str(ROOT / "hardware" / "kicad" / "canode.kicad_sch"))
    ap.add_argument("--ref", default="U1")
    a = ap.parse_args()
    if not a.netlist:
        a.netlist = str(Path(tempfile.gettempdir()) / "canode_check.net")
        subprocess.run(["kicad-cli", "sch", "export", "netlist", "-o", a.netlist, a.sch], check=True,
                       capture_output=True)
    pins, af = load_st(*ensure_st_data())
    nl = load_netlist(a.netlist, a.ref)
    fails, warns, rows = [], [], []

    for num, (net, kname) in sorted(nl.items(), key=lambda kv: int(kv[0])):
        if num == EXPOSED_PAD:
            ok = net.lstrip("/") == "GND"
            (rows if ok else fails).append(f"pin {num} exposed pad: on {net}" + ("" if ok else " (expected GND)"))
            continue
        cands = pins.get(num)
        if not cands:
            fails.append(f"pin {num}: not a pin position on {MCU_XML}"); continue
        # pick the ST entry whose base name matches the KiCad pin name (handles PA11/PA9 remap pairs)
        kbase = kname.split("/")[0].split("-")[0]
        st = next((c for c in cands if base_name(c[0]) == kbase), None)
        if st is None:
            fails.append(f"pin {num}: KiCad symbol says '{kname}', ST says {[c[0] for c in cands]}")
            st = cands[0]
        st_name, st_type, sigs = st
        b = base_name(st_name)
        if net.startswith("unconnected-"):
            continue
        if b in POWER:
            ok = net == POWER[b]
            (rows if ok else fails).append(f"pin {num} {b}: on {net}" + ("" if ok else f" (expected {POWER[b]})"))
            continue
        if net in SPECIAL:
            ok = SPECIAL[net] in st_name
            (rows if ok else fails).append(f"pin {num} {st_name}: {net}")
            continue
        req = REQUIREMENTS.get(net)
        if req is None:
            warns.append(f"pin {num} {b}: net '{net}' has no requirement entry - review it"); continue
        req = req if isinstance(req, list) else [req]
        hit = next((r for r in req if r in sigs), None)
        if hit is None:
            fails.append(f"pin {num} {b}: net {net} needs {' or '.join(req)}; pin offers "
                         f"{sorted(s for s in sigs if s != 'GPIO')}")
            continue
        if hit.startswith("SYS_SW"):
            afn = "(SWD is the default after reset)"
        else:
            afn = af.get((b, hit), "" if hit == "GPIO" else "(analog/system, no AF)")
        rows.append(f"pin {num:>2} {b:<5} {net:<11} -> {hit:<10} {afn}")

    missing = set(REQUIREMENTS) - {n for n, _ in nl.values()}
    for m in sorted(missing):
        fails.append(f"required net {m} is not connected to {a.ref}")

    print(f"Checked {a.ref} against ST {MCU_XML}\n")
    for r in rows: print("  OK  ", r)
    for w in warns: print("  WARN", w)
    for f in fails: print("  FAIL", f)
    print(f"\n{len(rows)} ok, {len(warns)} warnings, {len(fails)} failures")
    return 1 if fails else 0


if __name__ == "__main__":
    sys.exit(main())

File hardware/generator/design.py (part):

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   "33": "USB_DM", "34": "USB_DP", "35": "SWDIO", "36": "SWCLK",
   "38": "CAN1_RX", "39": "CAN1_TX", "40": "CAN1_STBY",
   "19": "CAN2_RX", "20": "CAN2_TX", "21": "CAN2_STBY",
   "45": "GPIO_PB6", "46": "GPIO_PB7", "47": "GPIO_PB8", "48": "GPIO_PB9"},
  (228.6, 132.08), (45.0, 18.0, 0))
C("C5", "100nF", "C14663", "+3V3", "GND", (190.5, 40.64), (49.5, 12.6, 0), mpn="CL10B104KB8NNNC")
C("C6", "4.7uF", "C1779", "+3V3", "GND", (200.66, 40.64), (52.5, 12.0, 90), fp=C0805, mpn="CL21A475KAQNNNE")
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  {"1": "GND", "2": "UART_TX", "3": "UART_RX"}, (281.94, 200.66), (48.0, 34.5, 0), jlc=False,
  desc="Debug UART (USART2): GND TX RX")
P("J5", "Connector_Generic:Conn_01x06", "GPIO", HDR.format(n=6), "", "1x6 2.54mm header",
  {"1": "+3V3", "2": "GPIO_PB6", "3": "GPIO_PB7", "4": "GPIO_PB8", "5": "GPIO_PB9", "6": "GND"},
  (281.94, 223.52), (60.0, 23.0, 90), jlc=False, desc="Spare GPIO (PB6/PB7 = I2C1 or USART1)")

# ---------------------------------------------------------------- CAN1 / CAN2
def can(n, y0, pcby):
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NOTES = [
    ((20.32, 25.4), "POWER: 12V > PTC > TVS > OR-ing > 3.3V LDO"),
    ((175.26, 25.4), "MCU: STM32G0B1 (2x FDCAN, USB FS crystal-less, 128K flash)"),
    ((302.26, 25.4), "CAN1 (FDCAN1 PD0/PD1) - default transceiver standby via R5 pull-up"),
    ((302.26, 93.98), "CAN2 (FDCAN2 PB0/PB1) - default transceiver standby via R7 pull-up"),
    ((302.26, 160.02), "USB-C (device, 5.1k Rd on CC)"),
    ((20.32, 147.32), "SENSE: VBAT / AUX_IN dividers 100k:10k (ADC full scale ~36V)"),
    ((20.32, 208.28), "AUX_OUT: low-side switch, 30V MOSFET, flyback to VBATF"),
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
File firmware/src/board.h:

/*
 * board.h - every difference between the supported boards lives here.
 *
 * Build defines exactly one of:
 *   BOARD_CANODE        canode rev A (STM32G0B1CEU6 UFQFPN-48, 2x SN65HVD230, 12 MHz crystal)
 *   BOARD_NUCLEO_G0B1RE ST NUCLEO-G0B1RE (MB1360) for testing before the PCB exists
 *
 * Pins that are the same on both boards (FDCAN, Rs, USART2) are defined once
 * at the bottom. On the Nucleo they are just morpho-header pins: there are no
 * transceivers, so only the internal-loopback self-test is meaningful there.
 * Pin map source of truth: firmware/README.md (checked by `make pins`).
 */
#ifndef BOARD_H
#define BOARD_H

#if defined(BOARD_CANODE)

#define BOARD_NAME           "canode-revA"
/* X1: 12 MHz crystal on PF0/PF1 (not an oscillator, so HSE is "on", not "bypass").
 * PLL M=3 gives the 4 MHz PLL input. */
#define BOARD_HSE_HZ         12000000u
#define BOARD_PLLM           RCC_PLLM_DIV3
#define BOARD_HAS_CAN_PHY    1    /* SN65HVD230 on both channels */

#define BOARD_LED1_PORT      GPIOA
#define BOARD_LED1_PIN       GPIO_PIN_5
#define BOARD_LED2_PORT      GPIOA
#define BOARD_LED2_PIN       GPIO_PIN_6
#define BOARD_LED_ON         GPIO_PIN_SET      /* active high */

/* Sleep wake-up for CAN2: PB0 is EXTI line 0, the same line as CAN1's PD0, and
 * EXTICR routes each line to one port only. PB0 is also COMP3_INP (IO1), and
 * COMP3 runs in Stop mode and wakes the chip through EXTI line 20, so CAN2
 * wakes through the comparator. See firmware/README.md "Sleep". */
#define BOARD_WAKE_CAN2_COMP 1

#elif defined(BOARD_NUCLEO_G0B1RE)

#define BOARD_NAME           "nucleo-g0b1re"
/* The Nucleo's HSE input (PF0) only gets the ST-LINK's 8 MHz MCO if solder
 * bridge SB17 is closed, and X3 is not fitted. ST's own Zephyr and TinyUSB board
 * files run it from HSI16, so do we: HSI16 / M=4 = the same 4 MHz PLL input.
 * HSI16 is +-1 %, fine for internal loopback but too loose for a real bus. */
#define BOARD_HSE_HZ         0u          /* 0 = no HSE, use HSI16 */
#define BOARD_PLLM           RCC_PLLM_DIV4
#define BOARD_HAS_CAN_PHY    0           /* no transceivers on the Nucleo */

/* LD4 (green, user) on PA5 via a transistor, active high. Only one user LED. */
#define BOARD_LED1_PORT      GPIOA
#define BOARD_LED1_PIN       GPIO_PIN_5
#define BOARD_LED_ON         GPIO_PIN_SET
/* No LED2. */

/* No transceiver drives PB0 here: in analog mode (needed for COMP3) it would
 * float and wake the board at random. CAN1 (PD0, with a pull-up) and the
 * ST-LINK virtual COM port (PA3) are the wake-up sources on the Nucleo. */
#define BOARD_WAKE_CAN2_COMP 0

#else
#error "Define BOARD_CANODE or BOARD_NUCLEO_G0B1RE"
#endif

/* HAL needs HSE_VALUE even if HSE is unused; 8 MHz = the Nucleo MCO value. */
#if BOARD_HSE_HZ
#define HSE_VALUE            BOARD_HSE_HZ
#else
#define HSE_VALUE            8000000u
#endif

/* ---- shared pin map (canode schematic; free morpho pins on the Nucleo) ---- */

/* FDCAN1 = CAN1 = car side. AF3 on PD0/PD1 (validated by `make pins`). */
#define BOARD_CAN1_PORT      GPIOD
#define BOARD_CAN1_RX_PIN    GPIO_PIN_0
#define BOARD_CAN1_TX_PIN    GPIO_PIN_1
#define BOARD_CAN1_AF        GPIO_AF3_FDCAN1
#define BOARD_CAN1_RS_PORT   GPIOD
#define BOARD_CAN1_RS_PIN    GPIO_PIN_2

/* FDCAN2 = CAN2 = module side. AF3 on PB0/PB1. */
#define BOARD_CAN2_PORT      GPIOB
#define BOARD_CAN2_RX_PIN    GPIO_PIN_0
#define BOARD_CAN2_TX_PIN    GPIO_PIN_1
#define BOARD_CAN2_AF        GPIO_AF3_FDCAN2
#define BOARD_CAN2_RS_PORT   GPIOB
#define BOARD_CAN2_RS_PIN    GPIO_PIN_2

/* USART2 on PA2 (TX) / PA3 (RX), AF1. canode: J4 header. Nucleo: ST-LINK VCP. */
#define BOARD_UART_PORT      GPIOA
#define BOARD_UART_TX_PIN    GPIO_PIN_2
#define BOARD_UART_RX_PIN    GPIO_PIN_3
#define BOARD_UART_AF        GPIO_AF1_USART2
#define BOARD_UART_BAUD      115200u

/* Power-on CAN defaults. Both channels come up in bus-monitoring (listen-only). */
#define BOARD_CAN_DEFAULT_BITRATE 500000u

/* Transceiver Rs state while monitoring (see can_rs_listen_t in can_drv.h):
 * CAN_RS_LISTEN_LOW  = transceiver active (current policy, CLAUDE.md)
 * CAN_RS_LISTEN_HIGH = transceiver standby: hardware TX-off, receiver on.
 * Stays LOW until the bring-up bench test (validation/README.md, bring-up
 * step 7) shows reception is reliable with Rs high at 125k-1M. Changing the
 * default is this one line; `rslisten` changes it at run time. */
#define BOARD_CAN_RS_LISTEN_DEFAULT CAN_RS_LISTEN_LOW

/* Sleep (STM32 Stop 1) when both buses have been quiet this long, no USB host
 * is connected and nothing is transmit-enabled. See lib/power.h and the
 * README "Sleep" section. `sleep on|off` and `sleep timeout <s>` change these
 * at run time (not saved). */
#define BOARD_SLEEP_DEFAULT_ENABLED   1
#define BOARD_SLEEP_DEFAULT_TIMEOUT_S 60u

#endif
